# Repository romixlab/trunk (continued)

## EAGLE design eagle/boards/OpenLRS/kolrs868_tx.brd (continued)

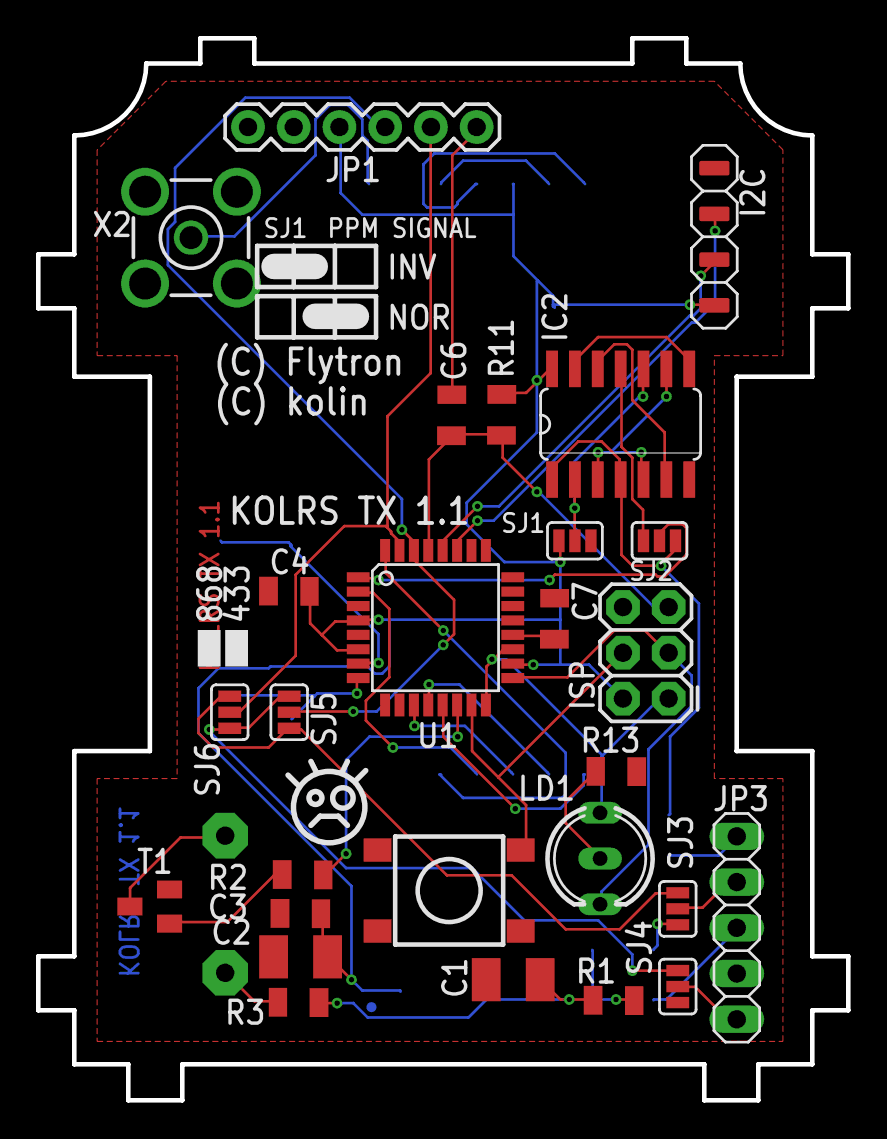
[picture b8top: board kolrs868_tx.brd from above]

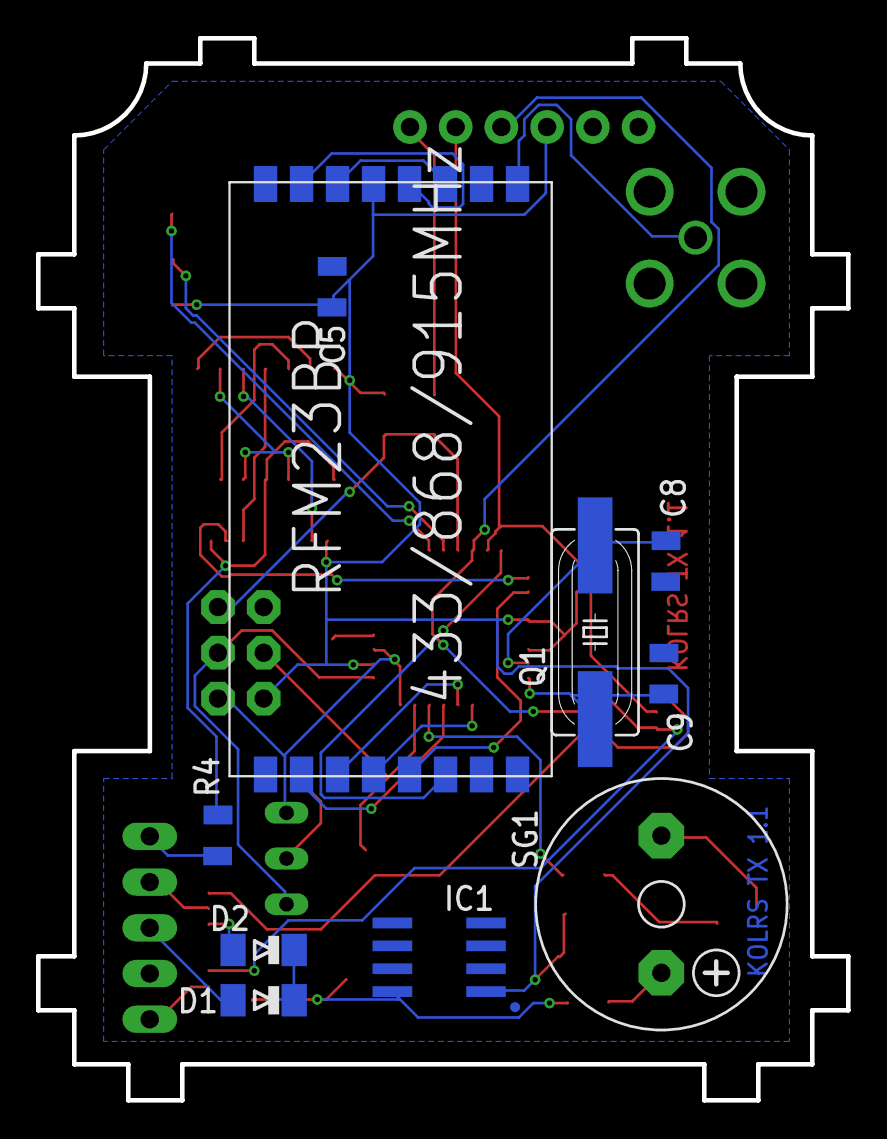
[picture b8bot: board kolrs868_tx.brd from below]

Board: 2 copper layers, 45.0 x 59.0 mm, 37 parts (10 on the bottom side), 43 nets.

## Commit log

2014-01-28 Update LICENSE
2014-01-28 added LampControll.qml and ToggleSwitch.qml
2014-02-05 added TB6560 rev2 board
2014-02-05 tb6560 update
2014-02-07 Add Erudite.SLDPRT
2014-02-24 add sim900 board
2014-02-25 update sim900
2014-08-03 added some boards
2014-08-25 added OpenLRS board; RFM23BP eagle lib; LampControll, ToggleSwitch to quick-tools
2014-08-25 removed build dir
2014-08-25 added ad folder
2014-08-26 OpenLRS rx board routed
2014-09-03 added qml play project
2014-09-03 automation play project added
2014-09-03 just some work with threads
2014-09-14 added pcb2din 55mm.SLDPRT
2014-09-28 added NCP1117, LM317, arduino pro mini to clamps and led (for door lock) boards, some changed in ras
2014-10-07 some work in ras
2014-10-11 dynamic slots and signals test
2014-10-20 some work in boards dynamic QObject implementation almost ready!
2015-03-16 Solid :: Subaru light
2015-03-17 TB6560 removed door lock removed Some old changes to ras (obsolete)
2015-03-17 RFR2 board
2015-03-17 Datasheets to RFR2 added
2015-03-18 Schematic work started
2015-05-14 uirs
2015-05-15 uirs work done, need testing
2015-05-17 cinematic (messages on top of video)
2015-05-17 some work
2015-06-06 CAT4101 simple board
2015-06-11 Fifty Fifty added - Simple app that makes time management more easy, it just counts to 50 min and then shows the window
2015-12-20 Add speed computation and batch processing.
